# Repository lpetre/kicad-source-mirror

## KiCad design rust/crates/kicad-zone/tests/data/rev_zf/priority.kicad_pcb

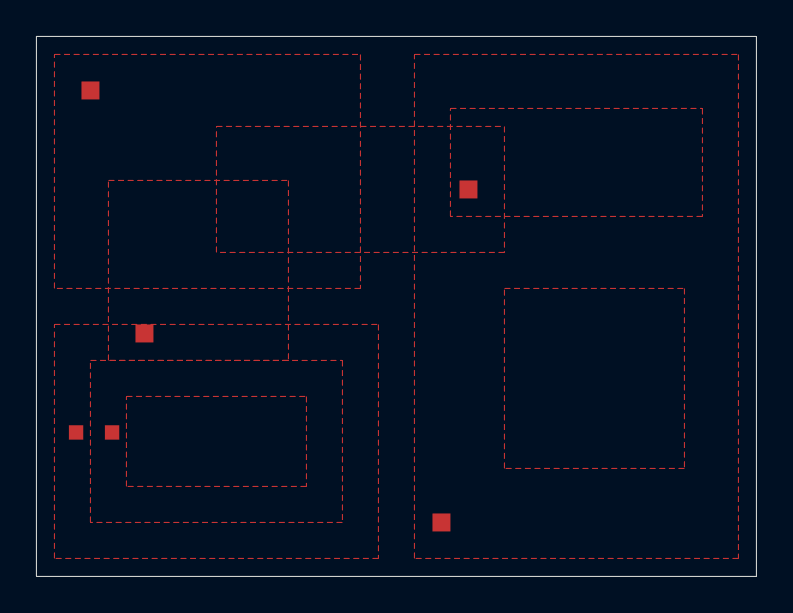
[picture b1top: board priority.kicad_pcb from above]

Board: 2 copper layers, 40.0 x 30.0 mm, 6 parts (0 on the bottom side), 3 nets, no tracks yet.

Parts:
P1: V; P1
P2: V; P2
P3: V; P3
P4: V; P4
P5: V; P5
P6: V; P6

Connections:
A: P1.1, P4.1
B: P2.1, P5.1
C: P3.1, P6.1

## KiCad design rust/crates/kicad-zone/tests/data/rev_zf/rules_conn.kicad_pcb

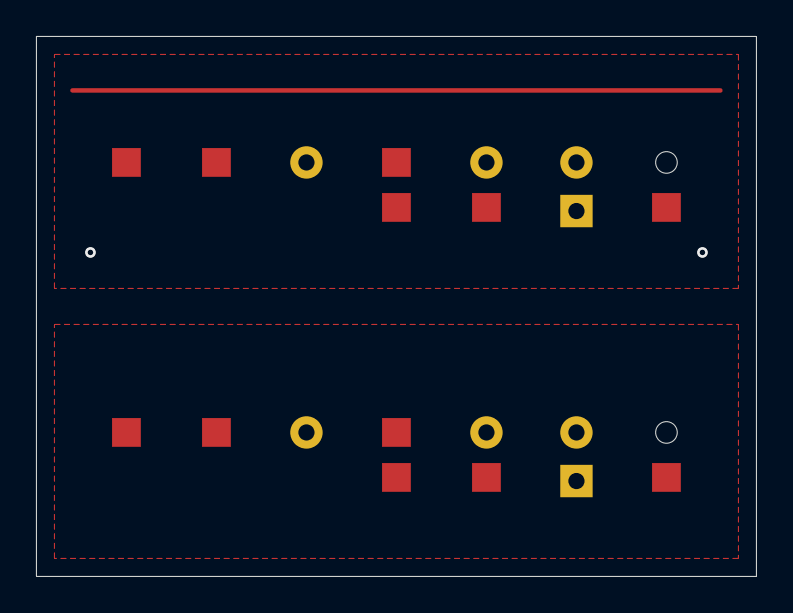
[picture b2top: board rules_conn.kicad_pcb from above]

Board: 2 copper layers, 40.0 x 30.0 mm, 14 parts (0 on the bottom side), 2 nets.

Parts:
R1a: V; R1a
R1b: V; R1b
R2a: V; R2a
R2b: V; R2b
R3a: V; R3a
R3b: V; R3b
R4a: V; R4a
R4b: V; R4b
R5a: V; R5a
R5b: V; R5b
R6a: V; R6a
R6b: V; R6b
R7a: V; R7a
R7b: V; R7b

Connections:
A: R1a.1, R1b.1, R2a.2, R2b.2, R3a.3, R3b.3, R4a.4, R4a.5, R4b.4, R4b.5, R5a.6, R5a.7, R5b.6, R5b.7, R6a.8, R6b.8, R7a.11, R7b.11
B: R6a.9, R6b.9
